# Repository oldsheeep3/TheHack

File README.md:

# HybridSwitcher — ハイブリッドIP映像スイッチャー

既存機材（ATEM Mini）と自作ハードウェア（自作スイッチングモジュール群 + Pico 2W）、
ネットワーク技術（SRT / NDI / WebAPI）を融合した、次世代のハイブリッドIP映像スイッチャーシステム。

PC上に常駐する制御アプリを「脳」とし、複数プロトコル（UVC / NDI / SRT）の映像入力・PiP合成・
仮想カメラ出力・タリー送出・外部機材（ATEM）の遠隔制御を一元化する。DIYでありながらプロ用
スイッチャーに匹敵する多人数オペレーション（メイン/サブ分業）と拡張性を目指す。

> 全体仕様は [`docs/specs/00-system-overview.md`](docs/specs/00-system-overview.md)（親仕様書）を参照。

## システム構成

```text
[ サブ ATEM Mini ] ──(SRT/HDMI/NDI)──→ [ メインPC (常駐App) ] ──(仮想WebCam/HDMI)──→ [ 配信/録画/OBS等 ]
        ▲                                    ▲        │
        │ (ATEM遠隔制御: UDP 9910)            │        │ (UDPタリー: 9999 ブロードキャスト)
        └────────────────────────────────────┘        ▼
                                             ▲   [ ワイヤレスタリー子機(ESP32) ]  [ 赤/緑 LED ]
                                             │ (WebSocket / WebAPI: 8080)
                                    (USB/HID/Serial)
[ 自作コントローラー: Pico 2W ] ──┬── (USB直結) ──→ メインPC
        │                         └── (USB-OTG) ──→ [ スマホ (Web App) ] ──(Wi-Fi/WebSocket)──→ メインPC
        │
        ├─(内部制御: 後日詳細化)──→ [ 各スイッチングモジュール内マイコン ]
        └─(HDMI DDC/I2Cスニッフィング)──→ [ 物理タリー抽出 ]
```

## コンポーネント

| コンポーネント | 場所 | 技術 | 責務 | 個別README / 仕様書 |
| --- | --- | --- | --- | --- |
| PC常駐アプリ | `src/` | C# / .NET 9 + **libobs**(P/Invoke) | 映像入力デコード・PiP合成・仮想カメラ/HDMI出力・WebAPI/WebSocket・UDPタリー送出・ATEM制御 | [App](src/Switcher.App/README.md) / [仕様](docs/specs/pc-switcher-app.md) / [移行](docs/specs/libobs-engine-migration.md) |
| ネイティブ映像エンジン | `native/switcher-engine/` | C/C++ + libobs (GPLv2) | libobs を駆動する `IVideoEngine` の実体（デュアルM/E=obs_view×2・ソース共有・出力・マルチビュー） | [switcher-engine](native/switcher-engine/README.md) |
| Pico 2W コントローラー | `firmware/pico2w-controller/` | Pico SDK (C/C++) | 物理ボタン入力→PC/スマホ送信・モジュール統括・HDMI DDCタリー抽出 | [Firmware](firmware/pico2w-controller/README.md) / [仕様](docs/specs/pico2w-controller-firmware.md) |
| スマホWebブリッジ | `apps/phone-bridge/` | React / TypeScript | Web Serial/WebUSBでPico 2Wを中継・ブラウザ設定UI | [phone-bridge](apps/phone-bridge/README.md) / [仕様](docs/specs/phone-web-bridge.md) |
| ワイヤレスタリー子機 | (未着手) | ESP32 (Arduino/ESP-IDF) | UDPブロードキャスト受信→赤/緑LED点灯 | [仕様](docs/specs/wireless-tally.md) |

### PC常駐アプリの .NET プロジェクト構成（`src/`）

| プロジェクト | 役割 |
| --- | --- |
| `Switcher.Contracts` | 共通インターフェース・DTO（`IVideoEngine` 抽象を含む契約層） |
| `Switcher.Engine` | `IVideoEngine` の実体。ネイティブ `switcher-engine`(libobs) への P/Invoke ＋ テスト用 `FakeVideoEngine` |
| `Switcher.Atem` | ATEM遠隔制御クライアント（UDP 9910） |
| `Switcher.Web` | WebAPI/WebSocketサーバ・UDPタリーブロードキャスト |
| `Switcher.App` | WPFホスト。上記を1つの常駐プロセスに結線するDI合成ルート |

> **libobs 移行**: 旧 `Switcher.Media`(GStreamer/DirectX 合成) / `Switcher.VirtualCam`(自作仮想カメラ) は廃止し、映像パスは libobs に一本化した（[`docs/specs/libobs-engine-migration.md`](docs/specs/libobs-engine-migration.md)）。ネイティブ `switcher-engine.dll` は Windows + OBS でのみビルド/実行し、`.sln` には含まない（テストは `FakeVideoEngine` 注入でヘッドレス実行）。

## リポジトリ構成

```text
.
├── src/                       # PC常駐アプリ (.NET 9) — HybridSwitcher.sln
├── native/switcher-engine/    # ネイティブ映像エンジン (C/C++ + libobs, CMake, .sln外)
├── tests/                     # 上記各プロジェクトのユニットテスト
├── apps/phone-bridge/         # スマホWebブリッジ & 設定UI (React/TS)
├── firmware/pico2w-controller/# Pico 2W コントローラー / タリー抽出ファーム
├── docs/
│   ├── specs/                 # 仕様書（親仕様書 + コンポーネント別）
│   └── tasks/                 # マルチエージェント実装計画・タスク指示書
├── softswitcher*/             # 既存KiCadハードウェア設計（参考資産）
└── HybridSwitcher.sln         # .NET ソリューション
```

## セットアップ（clone 直後に一度）

```sh
./setup.sh          # 共通（.NET / phone-bridge / firmware）
```

```powershell
.\setup.ps1         # Windows で映像エンジンまで動かす場合（追加で実行）
```

clone しただけの状態では、次の理由で初回ビルドが必ず落ちる。`setup.sh` がこれを一括で潰す。

| 落ちる理由 | `setup.sh` の対応 |
| --- | --- |
| `dotnet` / `node` が `~/.bashrc` 経由でしか PATH に乗らない（非ログインシェル・CI では不在） | `DOTNET_ROOT` と nvm を解決して検証。`--install-missing` で .NET SDK を `~/.dotnet` に導入 |
| `firmware/switcher-module/ch32v003fun` サブモジュールが未初期化 | `git submodule update --init --recursive` |
| `scripts` → `.claude/scripts` のリンク切れ（`.claude` は gitignore） | `.claude` を取得してリンクを復旧（失敗しても警告のみ。ビルドには不要） |
| NuGet / npm の依存が未取得 | `dotnet restore` と `npm ci`（CI と同じ lock 厳守） |

主なオプション（何度実行しても同じ結果になる）:

| オプション | 用途 |
| --- | --- |
| `--check` | 検証のみ。取得も生成もせず状態を報告する |
| `--ci` | 対話なし。`.env` を作らず、サブモジュールと `.claude` を触らない |
| `--install-missing` | .NET SDK が無ければ `dotnet-install.sh` で導入する |
| `--skip-submodules` / `--skip-restore` / `--skip-npm` / `--skip-agent-scripts` | 個別スキップ |

未解決の問題が残ると終了コード 1 で終わるので、CI からそのまま呼べる（`./setup.sh --ci`）。

### Windows でネイティブ映像エンジンまで用意する（`setup.ps1`）

Visual Studio で F5 したときの `DllNotFoundException` / `0x8007007E` は、ネイティブの `switcher-engine.dll` が未ビルドなことが原因。この DLL は `.sln` 外の CMake ビルドで、さらにその手前に libobs の import lib **`obs.lib`** が要る。`obs.lib` は **OBS のインストーラには含まれず**、OBS 本体をソースからビルドしないと手に入らない。

`setup.ps1` はその依存の連鎖を通しで面倒を見る。

```text
インストール済み OBS を検出 → 同じ版の obs-studio を clone
  → libobs だけビルド → obs.lib
    → .env に LIBOBS_* を記録
      → build.bat → switcher-engine.dll
        → Switcher.App.csproj が App 出力へ自動コピー（既存の仕組み）
```

| オプション | 用途 |
| --- | --- |
| `-Check` | 検証のみ。clone もビルドも `.env` の書き換えもしない |
| `-ObsVersion <version>` | 使う OBS の版を明示する |
| `-Force` | `obs-studio\` を作り直す（版を切り替えるとき） |
| `-Bundle` | `tools/bundle-obs-runtime.ps1` を呼び、App 出力に `obs-runtime\` を同梱する |
| `-SkipLibobs` / `-SkipEngine` | 個別スキップ |

> **初回は数十分かかる**（obs-studio の clone が数 GB、libobs のビルドがその後）。2 回目以降は済んだ工程を飛ばす。

**バージョンは固定していない。** マネージド側（`ObsRuntime.cs`）は libobs **30.0〜32.99** を受け入れ、範囲外でも警告を出すだけで拒否しない。`setup.ps1` もそれに合わせ、**インストール済み OBS の版を検出してその版のソースをビルドする**。OBS が入っていない場合だけ既定の **32.0.4**（実機検証済み）を使う。

> ⚠️ `obs.lib`（ビルド時）と `obs.dll`（実行時）の版が食い違うと起動失敗・クラッシュする。バージョンを検出に任せるのはこの事故を避けるため。手動で `-ObsVersion` を指定してインストール済みの版と食い違う場合は警告が出る。

**エンドユーザーは OBS のインストールが不要。** `ObsRuntime.Locate()` は実行ファイルの隣の `obs-runtime\` を最優先で見る（`ObsRuntime.cs:83-90`）ので、`-Bundle` で同梱した配布物は自己完結する。OBS インストールが要るのは**ビルドする側**だけ。

> **GPL**: `obs-runtime\` を同梱した配布物は GPL-2.0 になる。[`LICENSE`](LICENSE) / [`THIRD-PARTY-NOTICES.md`](THIRD-PARTY-NOTICES.md) 参照。

### 環境変数（`.env`）

ツールチェーン関連の変数は [`.env.example`](.env.example) をひな形に `.env` へ書く（`setup.sh` が無ければ自動生成する）。`.env` は gitignore 済み。既に export 済みの環境変数が `.env` より優先されるので、CI の `env:` / secrets が上書きされることはない。

> ⚠️ `.env` に書けるのは**ビルド/ツールチェーンの変数だけ**。アプリの動作設定（`AtemIp` / `WebPort` / `ProjectorDisplayIndex` 等）は `src/Switcher.App/appsettings.json` を `System.Text.Json` が直接読む実装で、環境変数は見ない（`Configuration/AppConfigLoader.cs`）。

## ビルド & テスト

### PC常駐アプリ（.NET 9）

> `./setup.sh` 済みでも、`dotnet` が PATH に乗るのは setup.sh の中だけ。呼び出し元のシェルには以下を前置きする。

```sh
export DOTNET_ROOT=$HOME/.dotnet PATH=$HOME/.dotnet:$PATH

dotnet build HybridSwitcher.sln     # 全プロジェクトのビルド
dotnet test  HybridSwitcher.sln     # 全ユニットテスト
```

`Switcher.App` は WPF (`net9.0-windows`) だが `EnableWindowsTargeting` によりLinuxでもCIでも
**コンパイルは可能**。ただしネイティブ `switcher-engine`(libobs) ランタイムは Windows 限定で、
**実行**には Windows 10/11 と下記の起動順が必要。

### ネイティブ映像エンジン（libobs）のビルド & Windows 実起動 — 起動順

`switcher-engine.dll`（`native/switcher-engine/`）は **Windows + OBS 専用**で `.sln` 外。以下が検証済みの順序
（詳細は [switcher-engine README](native/switcher-engine/README.md) / [L-002 タスク](docs/tasks/agent-L-002-native-libobs-engine.md)）。

> 以下は手順の内訳。**通常は [`setup.ps1`](#windows-でネイティブ映像エンジンまで用意するsetupps1) が 1〜2 を自動でやる**ので、手で追う必要があるのは仕組みを確認したいときだけ。

**前提**: Windows / Visual Studio 2022（「C++によるデスクトップ開発」）/ CMake ≥ 3.24 / インストール済み OBS（版は問わない。libobs 30.0〜32.99 が対象）。
以下はすべて **「x64 Native Tools Command Prompt for VS 2022」** から実行する（`cmake`/`cl` に PATH が通る。通常の cmd/PowerShell 不可）。

1. **libobs dev files を用意**（採用 OBS と**同一版**のソースをビルド。インストール済み OBS アプリだけではヘッダ/`obs.lib` が無い）
   ```bat
   git clone --recursive https://github.com/obsproject/obs-studio.git
   rem <version> はインストール済み OBS に合わせる（obs.dll のファイルバージョン）。
   cd obs-studio && git checkout <version> && git submodule update --init --recursive
   cmake --preset windows-x64
   cmake --build build_x64 --config Release --target libobs
   ```
   → `build_x64\libobs\Release\{obs.lib,obs.dll}`、生成ヘッダ `build_x64\config\obsconfig.h`、公開ヘッダ `libobs\`。

2. **`switcher-engine.dll` をビルド**（リポジトリルートで。ヘッダは公開＋生成の2フォルダを `;` 区切りで渡す）
   ```bat
   set OBS=<obs-studio のパス>
   set LIBOBS_INCLUDE_DIR=%OBS%\libobs;%OBS%\build_x64\config
   set LIBOBS_LIB=%OBS%\build_x64\libobs\Release\obs.lib
   native\switcher-engine\build.bat
   ```
   `Switcher.App.csproj` がビルド時に `switcher-engine.dll` を App 出力へ自動コピーする（VS F5/Rebuild でも維持）。

3. **App を起動**（`obs.dll` 等を PATH に通してから）
   - **Visual Studio**: 構成 `Debug`/**`x64`** → `Switcher.App` をスタートアップに → プロパティ「デバッグ」→ デバッグ起動プロファイルUIで環境変数
     `PATH = C:\Program Files\obs-studio\bin\64bit;%PATH%`（版一致のインストール済み OBS）→ **F5**。
   - **コマンドライン**:
     ```bat
     dotnet build src\Switcher.App\Switcher.App.csproj -c Release
     set PATH=%OBS%\build_x64\rundir\Release\bin\64bit;%PATH%
     src\Switcher.App\bin\x64\Release\net9.0-windows\Switcher.App.exe
     ```

> **前提/注意**
> - `obs.dll` + `data\` + プラグイン + `libobs-d3d11.dll` が PATH 上で到達可能、かつ import lib(`obs.lib`) と**同一版**であること（不一致は起動失敗/クラッシュ）。
> - **L-002 未完のうちは `engine_startup` が `obs_reset_video` で失敗**する（libobs データパス未配線。[L-002 タスク](docs/tasks/agent-L-002-native-libobs-engine.md)の「実機検証で判明した実装ポイント」参照）。
> - ネイティブ抜きで App を動かすなら DI（`src/Switcher.App/Composition/ServiceCollectionExtensions.cs`）を `FakeVideoEngine` に差し替える。

### スマホWebブリッジ（React/TS）

```sh
cd apps/phone-bridge
npm install
npm run dev      # 開発サーバ
npm run build    # プロダクションビルド
npm test         # vitest
```

### Pico 2W ファームウェア

I/Oに依存しないロジックはホストの `gcc` でユニットテスト可能（Pico SDK不要）。

```sh
cd firmware/pico2w-controller/test
make             # ビルド + 実行（全テスト green で終了コード0）
```

実機向けクロスビルド（Pico SDK / `arm-none-eabi` ツールチェーン必要）は
[`firmware/pico2w-controller/README.md`](firmware/pico2w-controller/README.md) を参照。

### CI（GitHub Actions）

[`.github/workflows/ci.yml`](.github/workflows/ci.yml) が **全 PR**（タスク → 親Epic の PR も含む）と
`main` / `develop` への push で走る。すべて `ubuntu-latest`。

| ジョブ | 内容 |
| --- | --- |
| `.NET` | `dotnet build -c Release -warnaserror` → `dotnet format --verify-no-changes` → `dotnet test`（結果 `.trx` をアーティファクト化） |
| `phone-bridge` | `npm ci` → `npm run lint`(eslint) → `npm run build`(`tsc -b` 型チェック + vite) → `npm test`(vitest)、`dist/` をアーティファクト化 |
| `firmware` | `firmware/pico2w-controller/test` と `firmware/switcher-module/test` のホストテスト（gcc、`-Werror`） |

ブランチ保護の必須チェックには集約ジョブ **`All checks`** 1つを指定すればよい。

**CI が走るのは個人リポジトリ（public）だけ。** ミラー先の `NxTEND-THE-HACK/2026-Team-38` は
Free org の private リポジトリで Actions のランナーが割り当てられず、どのジョブも 0 ステップの
まま即座に失敗する（ワークフロー側の問題ではなく org の Actions 枠の問題で、修正には org 管理者
による支払い設定・repo の public 化・セルフホストランナー登録のいずれかが要る）。そのため全ジョブに
`if: github.repository_owner != 'NxTEND-THE-HACK'` を付けて向こうでは skip させている。ジョブレベルの
`if` はランナー要求より前に評価されるので、skip されたジョブは失敗扱いにならない。

CI 対象外（ローカル/Windows でのみ検証可能）:

- `native/switcher-engine`（libobs 依存・Windows + OBS 専用・`.sln` 外）と、それを要する App の実起動
- `web/build-preview.ps1`（Windows PowerShell 前提のパス処理）
- `apps/phone-bridge` の Prettier 整形チェック（既存ファイルが未整形のため未導入。`npm run format` で一括整形後に追加可能）

### ミラー（個人リポジトリ → ハッカソン用リポジトリ）

開発を個人アカウントの public リポジトリ（`oldsheeep3/TheHack`）で行い、ハッカソン用 private
リポジトリ（`NxTEND-THE-HACK/2026-Team-38`）へ push のたびに反映する。**片方向**（個人 → ハッカソン用）。

**ミラー先へ書けるトークンは GitHub に預けない。** 実際に push するのは tailnet 上の VPS（`gh`
ログイン済み）で、自分の資格情報を使う。GitHub Actions はその VPS に SSH して起動をかけるだけ
なので、この public リポジトリに置く secret は tailnet への参加情報と SSH 鍵だけで済む。

`.github/` を含め、履歴をそのまま送る（コミット SHA も個人リポジトリ側と一致する）。ミラー先では
CI を走らせないよう、[`ci.yml`](.github/workflows/ci.yml) と [`mirror.yml`](.github/workflows/mirror.yml)
の両方がリポジトリのオーナーを見てジョブを skip する。

```text
手元 ── git push origin ──→ oldsheeep3/TheHack (public)
                              ├ Actions: ci.yml（green になったら↓を起動）
                              └ Actions: mirror.yml
                                  ├ tailscale/github-action で tailnet に参加
                                  └ ssh ──→ VPS: mirror-sync <branch>
                                              ├ 個人リポジトリから fetch（~/mirror/TheHack.git）
                                              └ mirror.sh  … mirror/X を push + PR 作成 + マージ
                                                              ↓
                                              NxTEND-THE-HACK/2026-Team-38 (private)
```

ブランチ `X` を push すると:

0. まず CI が走り、**green で終わったときだけ**ミラーが起動する（`workflow_run` トリガー）。
   赤い場合・CI が走らないブランチは、直さない限りミラーされない
1. [`.github/workflows/mirror.yml`](.github/workflows/mirror.yml) が tailnet に ephemeral ノードとして参加し、
   VPS へ SSH して [`mirror-sync X`](tools/mirror/mirror-sync) を実行する（CI が通った `X` だけが対象）
2. VPS が個人リポジトリから `X` を fetch し、[`tools/mirror/mirror.sh`](tools/mirror/mirror.sh) を呼ぶ
3. ミラー先の **`mirror/X`**（ミラー専用ブランチ）へ push
4. `mirror/X` → `X` の PR を作成（既にオープンならそれを使う）し、**マージコミットでマージする**

起点が GitHub 側にあるので、どのマシンから push しても（GitHub 上で直接編集しても）ミラーされる。
同期するのは CI が通ったそのブランチだけ。全ブランチ + 全タグをまとめて送るのは手動実行のとき。

ミラー先の `main` / `develop` へ直接 push も force push もしない。force は「手元で rebase / amend して
`mirror/X` が fast-forward できなくなった」場合のフォールバックとして `mirror/*` に対してのみ使う。
ミラー先の ref を削除することはないので、ブランチ削除は同期されない。

Actions が使えないとき（ワークフローの失敗、tailnet の不調、初回の一括コピー）は VPS 側で
`mirror-sync` を直接実行すれば追いつく。

| 場所 | もの | 役割 |
| --- | --- | --- |
| GitHub | `.github/workflows/mirror.yml` | tailnet に参加して VPS へ SSH し `mirror-sync` を起動 |
| VPS | `~/mirror/TheHack.git` | 中継用の bare リポジトリ（remote: `personal` / `hackathon`） |
| VPS | `~/mirror/mirror.sh` | `mirror/X` の push・PR 作成・マージ（[`tools/mirror/mirror.sh`](tools/mirror/mirror.sh)） |
| VPS | `~/.local/bin/mirror-sync` | 個人リポジトリから取り込んで同期（[`tools/mirror/mirror-sync`](tools/mirror/mirror-sync)） |

セットアップ:

```sh
# VPS 側（gh でログイン済み・gh auth setup-git 済みであること）
scp -r tools/mirror <vps>:~/mirror-install
ssh <vps> 'bash ~/mirror-install/install-vps.sh'

# CI 用の SSH 鍵を作って公開鍵を VPS に置く
ssh-keygen -t ed25519 -N '' -f mirror_ci
ssh-copy-id -i mirror_ci.pub <vps>

# 手動同期（全ブランチ + 全タグ / ブランチ指定）
ssh sheep 'bash -lc mirror-sync'
ssh sheep 'bash -lc "mirror-sync develop"'
```

個人リポジトリの Settings → Secrets and variables → Actions に登録する secret:

| secret | 中身 |
| --- | --- |
| `TS_CLIENT` / `TS_SECRET` | Tailscale の OAuth クライアント ID / シークレット（scope `auth_keys` write / tag `tag:ci`） |
| `SSH_HOST` / `SSH_USER` | VPS の tailnet アドレス（100.x or MagicDNS 名）とログインユーザー名 |
| `SSH_KEY` | ログインに使う**秘密鍵**（`mirror_ci` の中身。公開鍵は VPS の `authorized_keys` へ） |
| `SSH_KNOWN_HOSTS` | VPS のホスト鍵（`ssh-keyscan <host>` の出力）。任意だが推奨 |

tailnet の ACL で `tag:ci` から VPS の 22/tcp を許可しておくこと。

> - マージは **マージコミット**で行う（squash / rebase merge だと merge-base が進まず、次回の
>   PR に同じコミットが再び載る）。ブランチ保護で弾かれた場合は `gh pr merge --admin` で通す。
> - ミラー先に同名ブランチが無いと PR は作れない（`mirror/X` の push だけ行い notice を出す）。
>   その場合はミラー先で `mirror/X` からブランチを作る。
> - 手動で `mirror-sync` を叩くときは Actions の実行と重ならないようにする（作業リポジトリを共有
>   していて、排他はしていない）。
> - `workflow_run` は**デフォルトブランチにあるワークフローファイル**しか起動しない。`mirror.yml`
>   は `main` にも入っている必要がある（`develop` だけに置いても発火しない）。
> - CI の push トリガーは `main` / `develop` だけなので、作業ブランチを直接 push してもミラーは
>   起動しない（PR を出せば CI は走るが、`pull_request` 由来の実行はミラーの対象外）。作業ブランチを
>   今すぐミラーしたいときは VPS で `mirror-sync <branch>` を叩くか、Actions から手動実行する。
> - ミラーの実行は `concurrency` で 1 本に絞っている。実行中 + 待機中がいる状態でさらに CI が
>   green になると待機中が追い出され、そのブランチは次の CI green まで待つ。
> - `.github/workflows/` も同期するので、VPS の `gh` ログインには **`workflow` スコープ**が要る
>   （`gh auth refresh -h github.com -s workflow`）。無いと push が拒否される。
> - タグは手動同期（引数なしの `mirror-sync`）のときにまとめて送る。ミラー先で既に別のコミットを
>   指しているタグは上書きしない。

## 共通プロトコル / ポート

各コンポーネントは親仕様書 §4 の共通定義に準拠する。

| ポート | プロトコル | 用途 |
| --- | --- | --- |
| 8080 | HTTP/WebSocket | 設定WebAPI・コントローラー入力受信 |
| 9000 | SRT (Listener) | 映像入力（ATEM PGM等） |
| 9999 | UDP broadcast | タリー配信（`255.255.255.255:9999`） |
| 9910 | UDP | ATEM遠隔制御（ATEM純正プロトコル） |

詳細（イベントペイロード・設定変更API・タリーペイロード）は
[`docs/specs/00-system-overview.md`](docs/specs/00-system-overview.md) §4 を参照。

## ドキュメント

- **技術仕様（現行実装）**: [`docs/spec/technical-overview.md`](docs/spec/technical-overview.md)（詳細） /
  [`docs/spec/summary.md`](docs/spec/summary.md)（要約） / [`docs/slides/switcher.md`](docs/slides/switcher.md)（Marp）
- **配布サイト**: [`web/`](web/) — LP + 使い方（`web/build-preview.ps1` で1ファイルのプレビューを生成）
- **ライセンス**: GPL-2.0-or-later（[`LICENSE`](LICENSE) / [`THIRD-PARTY-NOTICES.md`](THIRD-PARTY-NOTICES.md)）
- **仕様書**: [`docs/specs/`](docs/specs/) — 親仕様書 + コンポーネント別詳細仕様
- **実装計画 / タスク**: [`docs/tasks/`](docs/tasks/) — マルチエージェント実装のオーケストレーション計画とタスク指示書

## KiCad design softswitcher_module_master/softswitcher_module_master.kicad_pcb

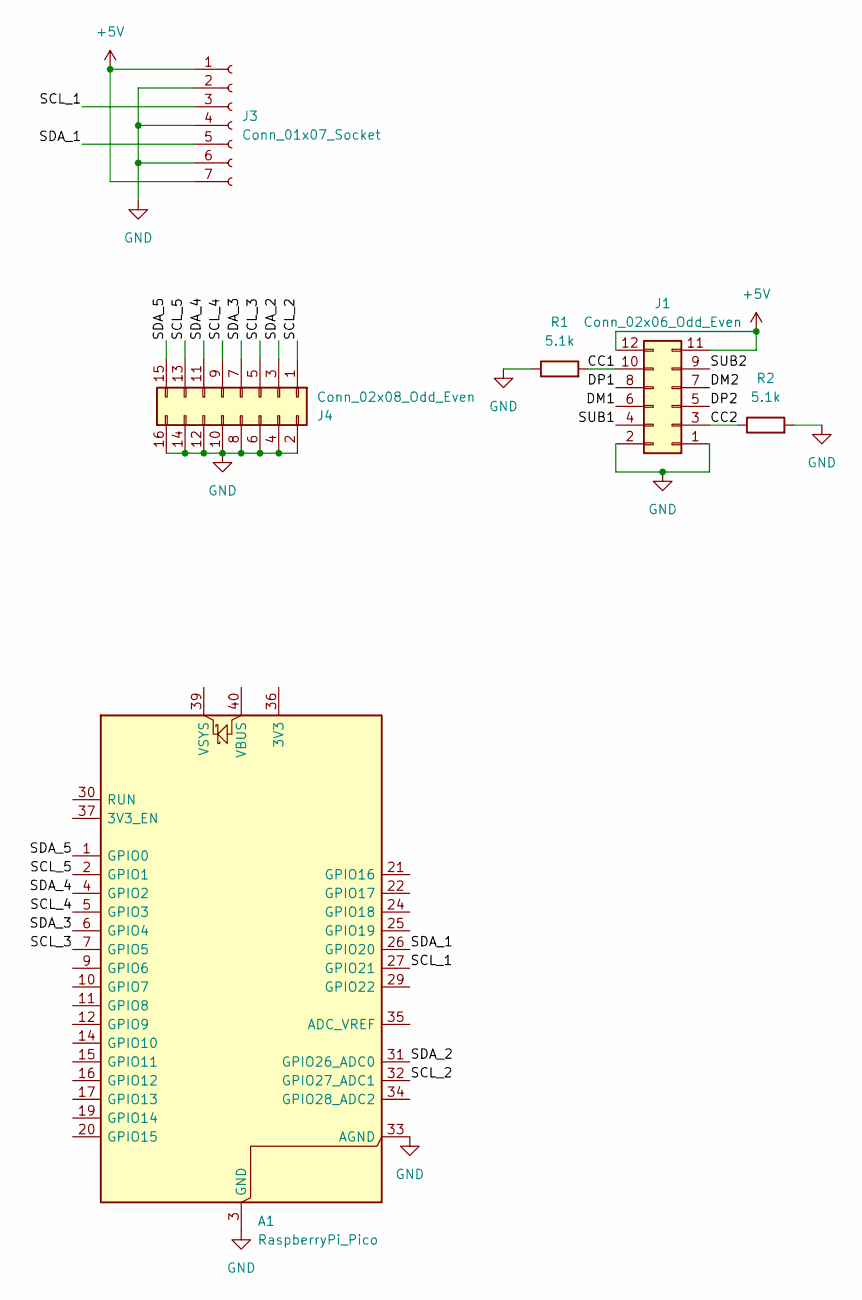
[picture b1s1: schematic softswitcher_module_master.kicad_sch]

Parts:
A1: RaspberryPi_Pico; RaspberryPi_Pico_Common_THT
J1: Conn_02x06_Odd_Even; PinHeader_2x06_P2.54mm_Vertical
J3: Conn_01x07_Socket; PinSocket_1x07_P2.54mm_Horizontal
J4: Conn_02x08_Odd_Even; PinSocket_2x08_P2.54mm_Horizontal
R1, R2: 5.1k; R_Axial_DIN0309_L9.0mm_D3.2mm_P12.70mm_Horizontal

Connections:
+5V: J1.11, J1.12, J3.1, J3.7
/CC1: J1.10, R1.2
/CC2: J1.3, R2.1
/DM1: J1.6
/DM2: J1.7
/DP1: J1.8
/DP2: J1.5
/SCL_1: A1.27 (GPIO21), J3.3
/SCL_2: A1.32 (GPIO27_ADC1), J4.1
/SCL_3: A1.7 (GPIO5), J4.5
/SCL_4: A1.5 (GPIO3), J4.9
/SCL_5: A1.2 (GPIO1), J4.13
/SDA_1: A1.26 (GPIO20), J3.5
/SDA_2: A1.31 (GPIO26_ADC0), J4.3
/SDA_3: A1.6 (GPIO4), J4.7
/SDA_4: A1.4 (GPIO2), J4.11
/SDA_5: A1.1 (GPIO0), J4.15
/SUB1: J1.4
/SUB2: J1.9
GND: A1.3 (GND), A1.8 (GND), A1.13 (GND), A1.18 (GND), A1.23 (GND), A1.28 (GND), A1.33 (AGND), A1.38 (GND), J1.1, J1.2, J3.2, J3.4, J3.6, J4.2, J4.4, J4.6, J4.8, J4.10, J4.12, J4.14, J4.16, R1.1, R2.2

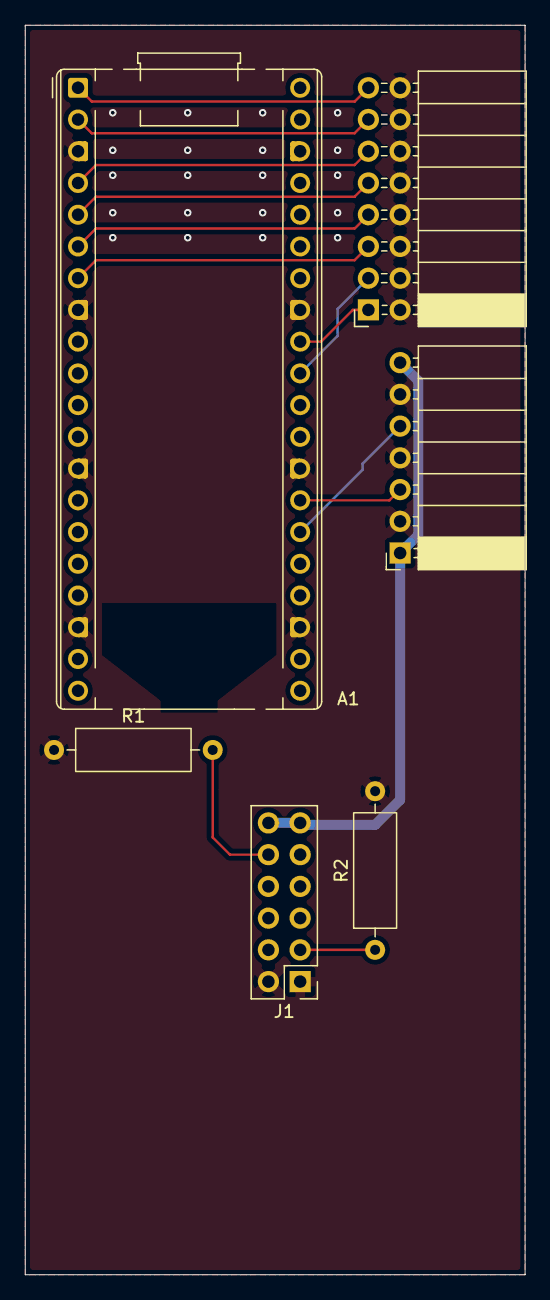
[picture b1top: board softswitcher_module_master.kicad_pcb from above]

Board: 2 copper layers, 40.0 x 100.0 mm, 6 parts (0 on the bottom side), 14 nets.

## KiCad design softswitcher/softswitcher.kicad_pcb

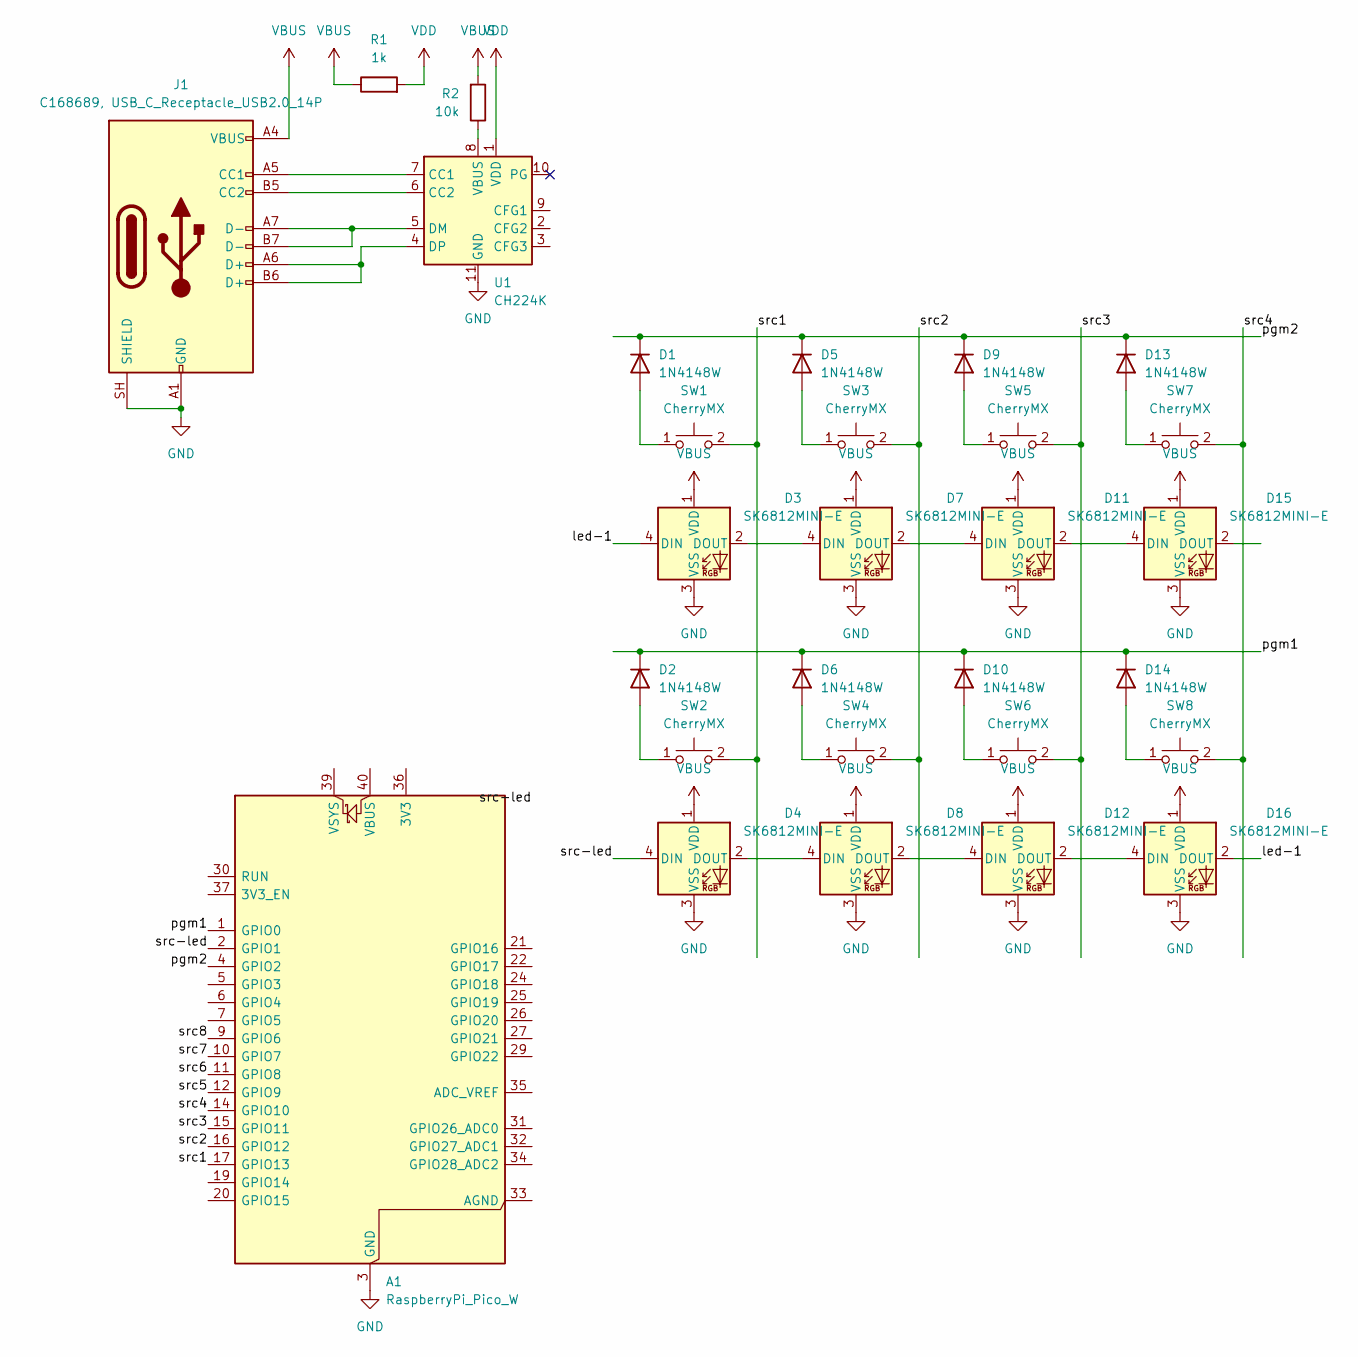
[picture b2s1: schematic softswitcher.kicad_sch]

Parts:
A1: RaspberryPi_Pico_W; RaspberryPi_Pico_Common_THT
D1, D2, D5, D6, D9, D10, D13, D14: 1N4148W; D_SOD-123
D3, D4, D7, D8, D11, D12, D15, D16: SK6812MINI-E; MX_SK6812MINI-E
J1: C168689, USB_C_Receptacle_USB2.0_14P; USB_C_Receptacle_GCT_USB4105-xx-A_16P_TopMnt_Horizontal
R1: 1k; R_1206_3216Metric
R2: 10k; R_1206_3216Metric
SW1, SW2, SW3, SW4, SW5, SW6, SW7, SW8: CherryMX; CherryMX_1.00u
U1: CH224K; SSOP-10-1EP_3.9x4.9mm_P1mm_EP2.1x3.3mm

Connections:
/led-1: D3.4 (DIN), D16.2 (DOUT)
/pgm1: A1.1 (GPIO0), D2.1 (K), D6.1 (K), D10.1 (K), D14.1 (K)
/pgm2: A1.4 (GPIO2), D1.1 (K), D5.1 (K), D9.1 (K), D13.1 (K)
/src1: A1.17 (GPIO13), SW1.2, SW2.2
/src2: A1.16 (GPIO12), SW3.2, SW4.2
/src3: A1.15 (GPIO11), SW5.2, SW6.2
/src4: A1.14 (GPIO10), SW7.2, SW8.2
/src5: A1.12 (GPIO9)
/src6: A1.11 (GPIO8)
/src7: A1.10 (GPIO7)
/src8: A1.9 (GPIO6)
/src-led: A1.2 (GPIO1), D4.4 (DIN)
GND: A1.3 (GND), A1.8 (GND), A1.13 (GND), A1.18 (GND), A1.23 (GND), A1.28 (GND), A1.38 (GND), D3.3 (VSS), D4.3 (VSS), D7.3 (VSS), D8.3 (VSS), D11.3 (VSS), D12.3 (VSS), D15.3 (VSS), D16.3 (VSS), J1.A1 (GND), J1.A12 (GND), J1.B1 (GND), J1.B12 (GND), J1.SH (SHIELD), U1.11 (GND)
unnamed: D1.2 (A), SW1.1
unnamed: D2.2 (A), SW2.1
unnamed: D3.2 (DOUT), D7.4 (DIN)
unnamed: D4.2 (DOUT), D8.4 (DIN)
unnamed: D5.2 (A), SW3.1
unnamed: D6.2 (A), SW4.1
unnamed: D9.2 (A), SW5.1
unnamed: D10.2 (A), SW6.1
unnamed: D7.2 (DOUT), D11.4 (DIN)
unnamed: D11.2 (DOUT), D15.4 (DIN)
unnamed: D8.2 (DOUT), D12.4 (DIN)
unnamed: D12.2 (DOUT), D16.4 (DIN)
unnamed: D13.2 (A), SW7.1
unnamed: D14.2 (A), SW8.1
unnamed: J1.A5 (CC1), U1.7 (CC1)
unnamed: J1.B5 (CC2), U1.6 (CC2)
unnamed: J1.A7 (D-), J1.B7 (D-), U1.5 (DM)
unnamed: J1.A6 (D+), J1.B6 (D+), U1.4 (DP)
unnamed: R2.1, U1.8 (VBUS)
VBUS: D3.1 (VDD), D4.1 (VDD), D7.1 (VDD), D8.1 (VDD), D11.1 (VDD), D12.1 (VDD), D15.1 (VDD), D16.1 (VDD), J1.A4 (VBUS), J1.A9 (VBUS), J1.B4 (VBUS), J1.B9 (VBUS), R1.1, R2.2
VDD: R1.2, U1.1 (VDD)

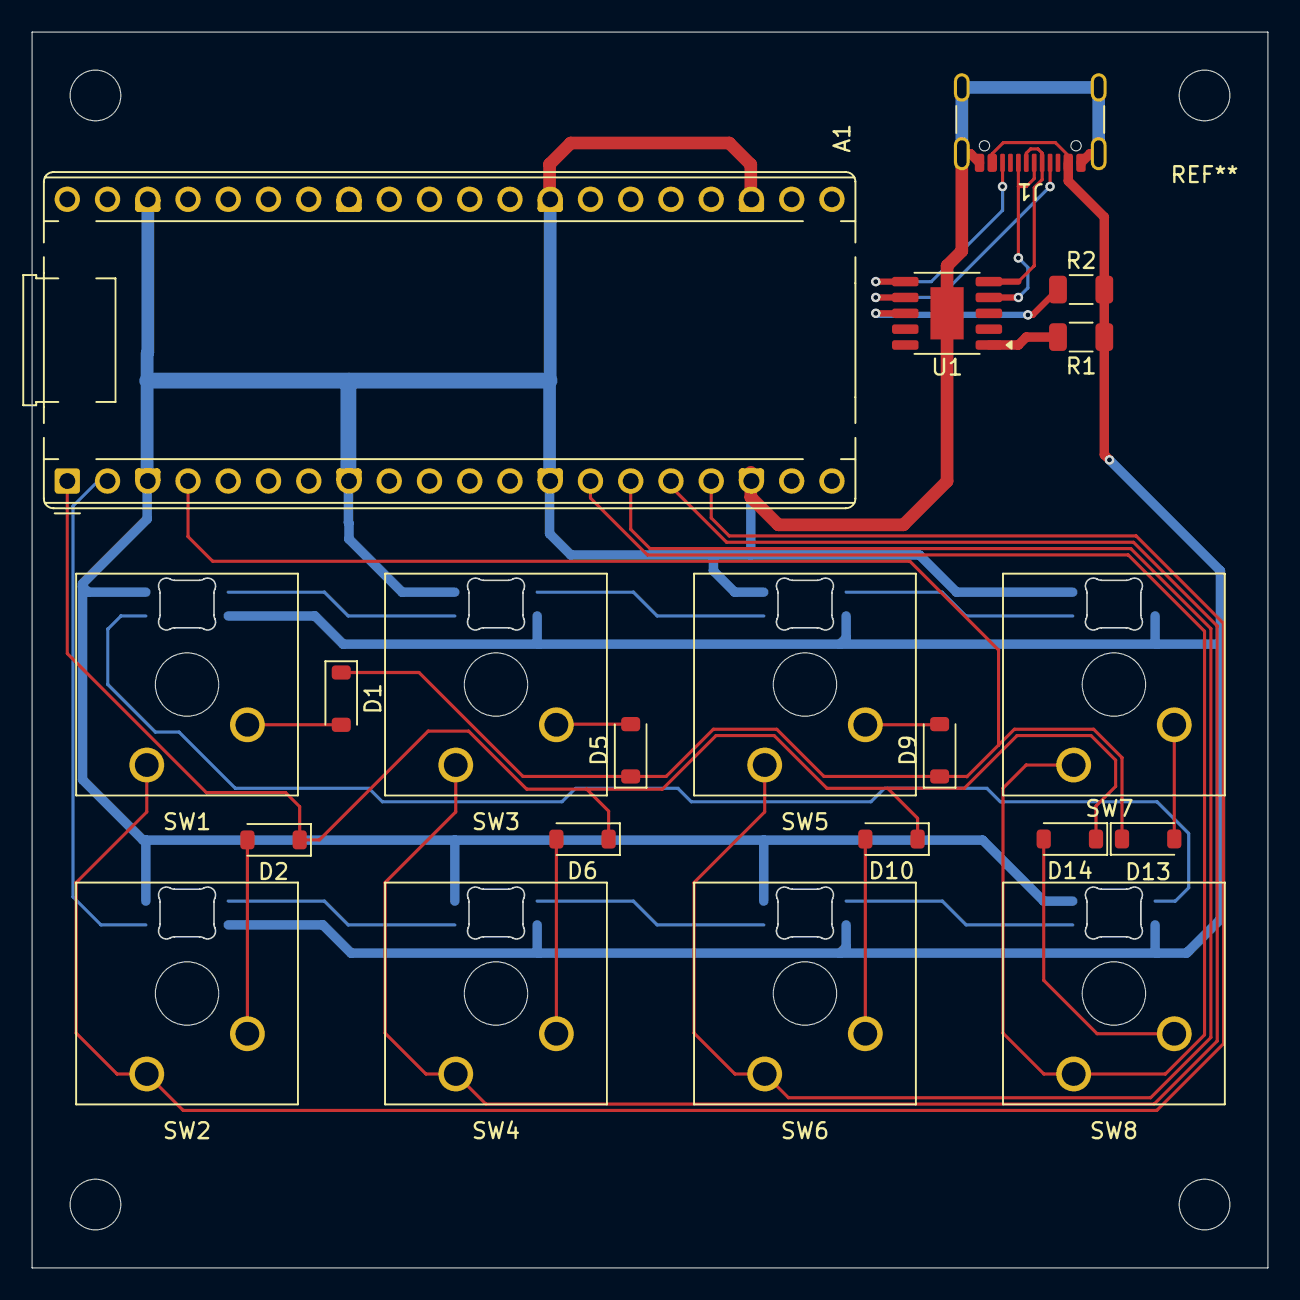
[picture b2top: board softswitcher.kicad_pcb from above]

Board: 2 copper layers, 78.0 x 78.0 mm, 29 parts (0 on the bottom side), 30 nets.

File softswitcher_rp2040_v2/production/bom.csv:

Designator,Footprint,Quantity,Value,LCSC Part #
A1,RaspberryPi_Pico_Common_THT,1,RaspberryPi_Pico_W,
"D1, D10, D13, D14, D2, D5, D6, D9",D_SOD-123,8,1N4148W,
"D11, D12, D15, D16, D3, D4, D7, D8",MX_SK6812MINI-E,8,SK6812MINI-E,
J1,USB_C_Receptacle_GCT_USB4105-xx-A_16P_TopMnt_Horizontal,1,USB_C_Receptacle_USB2.0_14P,
R1,1206,1,1k,
R2,1206,1,10k,
"SW1, SW2, SW3, SW4, SW5, SW6, SW7, SW8",CherryMX_1.00u,8,CherryMX,
U1,SSOP-10-1EP_3.9x4.9mm_P1mm_EP2.1x3.3mm,1,CH224K,

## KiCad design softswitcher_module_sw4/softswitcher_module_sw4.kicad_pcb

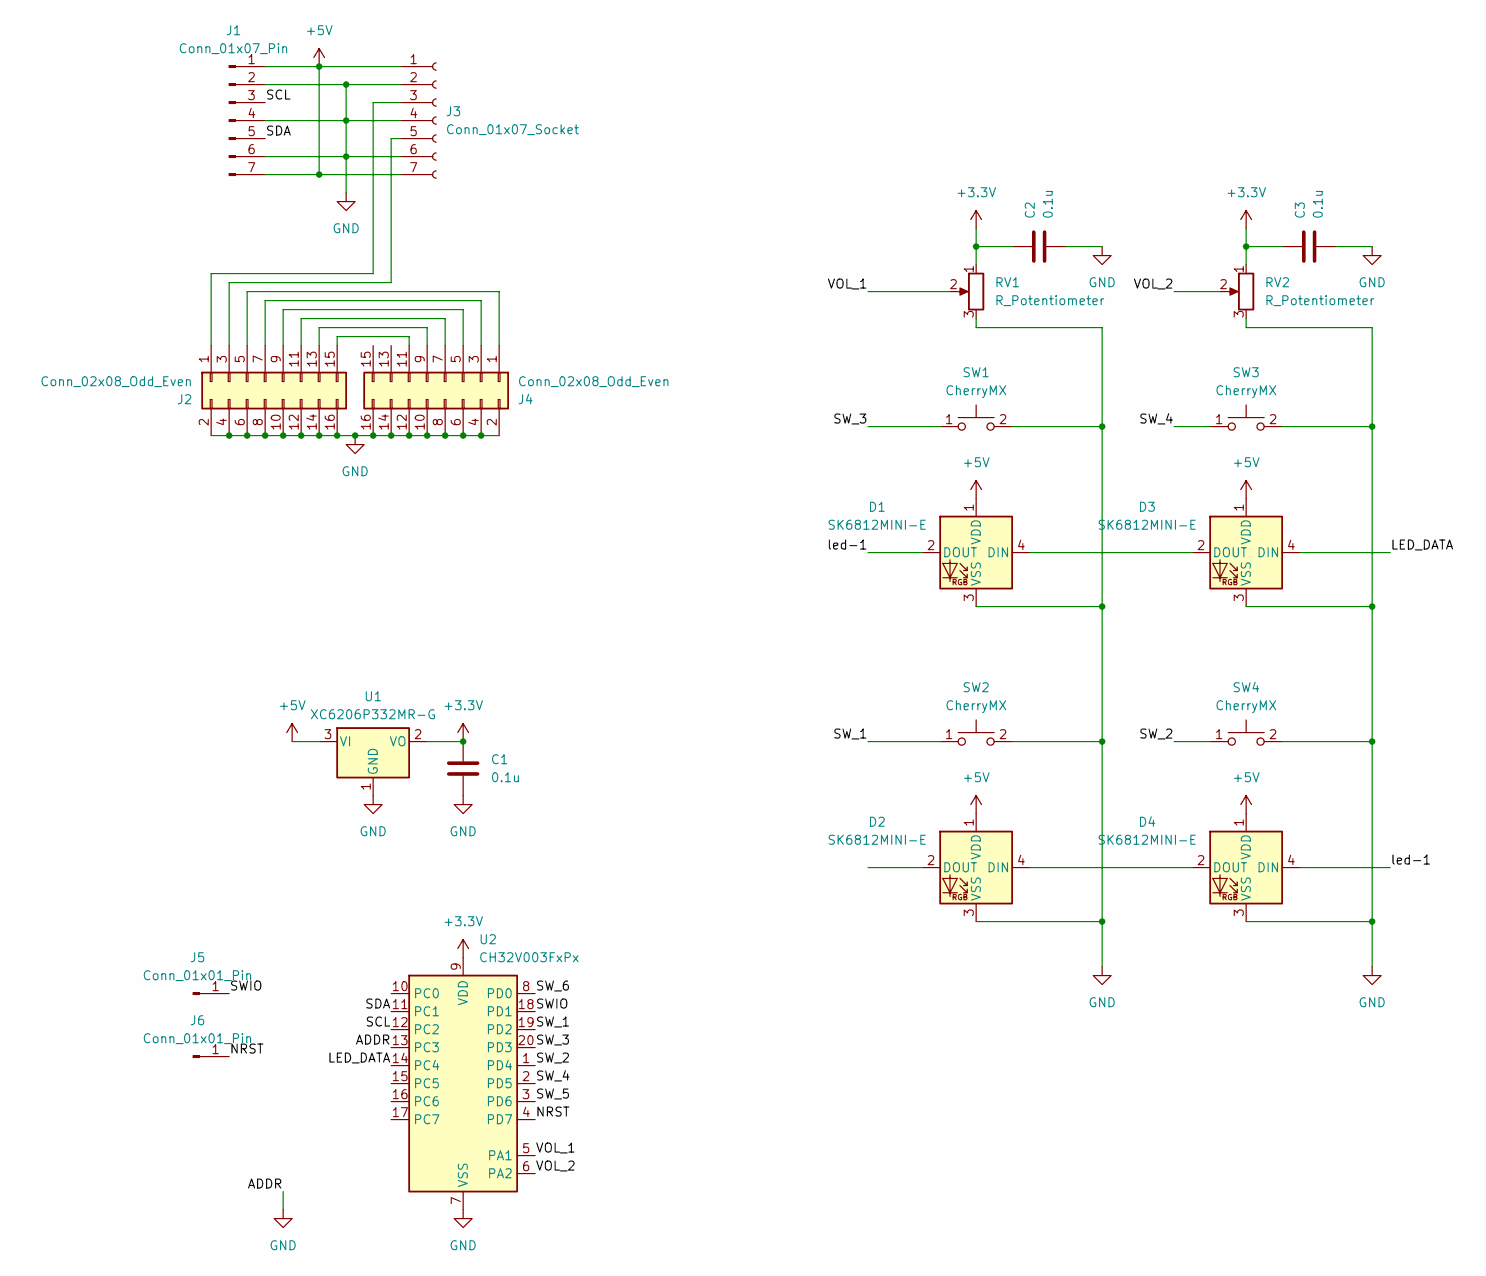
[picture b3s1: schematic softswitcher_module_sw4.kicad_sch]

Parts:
C1, C2, C3: 0.1u; C_0402_1005Metric
D1, D2, D3, D4: SK6812MINI-E; MX_SK6812MINI-E
J1: Conn_01x07_Pin; PinHeader_1x07_P2.54mm_Horizontal
J2: Conn_02x08_Odd_Even; PinHeader_2x08_P2.54mm_Horizontal
J3: Conn_01x07_Socket; PinSocket_1x07_P2.54mm_Horizontal
J4: Conn_02x08_Odd_Even; PinSocket_2x08_P2.54mm_Horizontal
J5, J6: Conn_01x01_Pin; PinHeader_1x01_P2.54mm_Vertical
RV1, RV2: R_Potentiometer; Potentiometer_Alps_RK09K_Single_Vertical
SW1, SW2, SW3, SW4: CherryMX; CherryMX_1.00u
U1: XC6206P332MR-G; SOT-23-3
U2: CH32V003FxPx; TSSOP-20_4.4x6.5mm_P0.65mm

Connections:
+3.3V: C1.1, C2.1, C3.1, RV1.1, RV2.1, U1.2 (VO), U2.9 (VDD)
+5V: D1.1 (VDD), D2.1 (VDD), D3.1 (VDD), D4.1 (VDD), J1.1, J1.7, J3.1, J3.7, U1.3 (VI)
/LED_DATA: D3.4 (DIN), U2.14 (PC4)
/NRST: J6.1 (Pin_1_1), U2.4 (PD7)
/SCL: J1.3, U2.12 (PC2)
/SDA: J1.5, U2.11 (PC1)
/SWIO: J5.1 (Pin_1_1), U2.18 (PD1)
/SW_1: SW2.1, U2.19 (PD2)
/SW_2: SW4.1, U2.1 (PD4)
/SW_3: SW1.1, U2.20 (PD3)
/SW_4: SW3.1, U2.2 (PD5)
/SW_5: U2.3 (PD6)
/SW_6: U2.8 (PD0)
/VOL_1: RV1.2, U2.5 (PA1)
/VOL_2: RV2.2, U2.6 (PA2)
/led-1: D1.2 (DOUT), D4.4 (DIN)
GND: C1.2, C2.2, C3.2, D1.3 (VSS), D2.3 (VSS), D3.3 (VSS), D4.3 (VSS), J1.2, J1.4, J1.6, J2.2, J2.4, J2.6, J2.8, J2.10, J2.12, J2.14, J2.16, J3.2, J3.4, J3.6, J4.2, J4.4, J4.6, J4.8, J4.10, J4.12, J4.14, J4.16, RV1.3, RV2.3, SW1.2, SW2.2, SW3.2, SW4.2, U1.1 (GND), U2.7 (VSS), U2.13 (PC3)
unnamed: D1.4 (DIN), D3.2 (DOUT)
unnamed: D2.4 (DIN), D4.2 (DOUT)
unnamed: J2.1, J3.3
unnamed: J2.3, J3.5
unnamed: J2.5, J4.1
unnamed: J2.7, J4.3
unnamed: J2.9, J4.5
unnamed: J2.11, J4.7
unnamed: J2.13, J4.9
unnamed: J2.15, J4.11

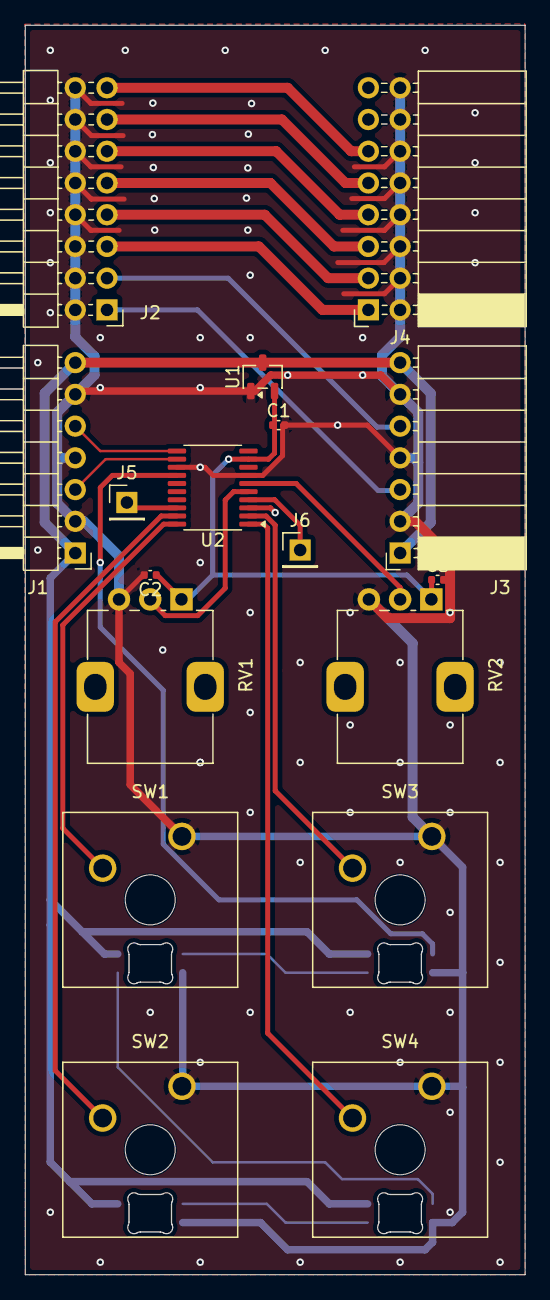
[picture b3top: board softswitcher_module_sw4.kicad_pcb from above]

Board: 2 copper layers, 40.0 x 100.0 mm, 21 parts (0 on the bottom side), 25 nets.

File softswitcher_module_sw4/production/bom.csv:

Designator,Footprint,Quantity,Value,LCSC Part #
"C1, C2, C3",0402,3,0.1u,
J1,PinHeader_1x07_P2.54mm_Horizontal,1,Conn_01x07_Pin,
J2,PinHeader_2x08_P2.54mm_Horizontal,1,Conn_02x08_Odd_Even,
J3,PinSocket_1x07_P2.54mm_Horizontal,1,Conn_01x07_Socket,
J4,PinSocket_2x08_P2.54mm_Horizontal,1,Conn_02x08_Odd_Even,
"J5, J6",PinHeader_1x01_P2.54mm_Vertical,2,Conn_01x01_Pin,
"SW1, SW2, SW3, SW4",CherryMX_1.00u,4,CherryMX,
U1,SOT-23-3,1,XC6206P332MR-G,
U2,TSSOP-20_4.4x6.5mm_P0.65mm,1,CH32V003FxPx,

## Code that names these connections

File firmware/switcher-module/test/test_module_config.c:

// module_config.h の定数実体 (module_config.c) がSW/VR/バックライト/I2Cベースアドレスの
// 契約どおりに提供されていることを検証する。ピン番号は基板 softswitcher_module_sw4
// (CH32V003F4P6, TSSOP-20) の実配線。

#include <assert.h>
#include <stdio.h>

#include "module_config.h"

// ch32fun のピンエンコード (ポート番号<<4 | ピン番号) の実値。ch32fun.h をincludeせずに
// 検証できるよう期待値をリテラルで置く (ch32fun定数との一致は switches.c /
// backlight.c / i2c_slave.c の _Static_assert がクロスビルド時に保証する)。
#define EXPECT_PA1 0x01
#define EXPECT_PC1 0x21
#define EXPECT_PC2 0x22
#define EXPECT_PC4 0x24
#define EXPECT_PD2 0x32
#define EXPECT_PD3 0x33
#define EXPECT_PD4 0x34
#define EXPECT_PD5 0x35

int main(void) {
    assert(MAX_MODULES == 8);
    assert(I2C_BASE_ADDR == 0x30);

    // ピンエンコードが ch32fun (GpioOf: pin>>4 でポート, pin&0xf でビット) と同形式。
    assert(MODULE_PIN(MODULE_PORT_A, 1) == EXPECT_PA1);
    assert(MODULE_PIN(MODULE_PORT_C, 4) == EXPECT_PC4);
    assert(MODULE_PIN(MODULE_PORT_D, 2) == EXPECT_PD2);

    // I2Cスレーブ: 11pin(PC1)=SDA / 12pin(PC2)=SCL (I2C1のシリコン固定ピン)。
    assert(MODULE_I2C_SDA_PIN == EXPECT_PC1);
    assert(MODULE_I2C_SCL_PIN == EXPECT_PC2);

    // SW: 4個の独立入力。SW_1=19pin(PD2) / SW_2=1pin(PD4) / SW_3=20pin(PD3) / SW_4=2pin(PD5)。
    assert(SW_COUNT == 4);
    assert(SW_BIT_SW1 == 0);
    assert(SW_BIT_SW2 == 1);
    assert(SW_BIT_SW3 == 2);
    assert(SW_BIT_SW4 == 3);
    assert(SW_BIT_PGM1_SRC1 == SW_BIT_SW1);
    assert(SW_BIT_PGM1_SRC2 == SW_BIT_SW2);
    assert(SW_BIT_PGM2_SRC1 == SW_BIT_SW3);
    assert(SW_BIT_PGM2_SRC2 == SW_BIT_SW4);
    assert(sizeof(SW_PINS) / sizeof(SW_PINS[0]) == SW_COUNT);
    assert(SW_PINS[SW_BIT_SW1] == EXPECT_PD2);
    assert(SW_PINS[SW_BIT_SW2] == EXPECT_PD4);
    assert(SW_PINS[SW_BIT_SW3] == EXPECT_PD3);
    assert(SW_PINS[SW_BIT_SW4] == EXPECT_PD5);

    // VR: VOL1=5pin(PA1)=ADCチャネル1 / VOL2=6pin(PA2)=ADCチャネル0。
    assert(VR_COUNT == 2);
    assert(sizeof(VR_ADC_CHANNELS) / sizeof(VR_ADC_CHANNELS[0]) == VR_COUNT);
    assert(VR_ADC_CHANNELS[VR_SRC1_INDEX] == 1);
    assert(VR_ADC_CHANNELS[VR_SRC2_INDEX] == 0);

    // バックライト: LED_DATA=14pin(PC4), SK6812MINI-E ×4。
    assert(BACKLIGHT_LED_COUNT == 4);
    assert(BACKLIGHT_DATA_PIN == EXPECT_PC4);
    assert(MODULE_REG_BACKLIGHT_LEN == BACKLIGHT_LED_COUNT * 3);

    // モジュール番号ストラップは実基板に無く、全モジュールが 0x30 固定で待ち受ける。
    assert(MODULE_INDEX_FIXED == 0);

    // ピンの重複割当が無いこと (SW×4 + LED_DATA + I2C×2)。
    const uint8_t all_pins[] = {
        SW_PINS[0], SW_PINS[1], SW_PINS[2], SW_PINS[3],
        BACKLIGHT_DATA_PIN, MODULE_I2C_SDA_PIN, MODULE_I2C_SCL_PIN,
    };
    const unsigned all_pin_count = sizeof(all_pins) / sizeof(all_pins[0]);
    for (unsigned i = 0; i < all_pin_count; i++) {
        for (unsigned j = i + 1; j < all_pin_count; j++) {
            assert(all_pins[i] != all_pins[j]);
        }
    }
    printf("test_module_config: OK\n");
    return 0;
}

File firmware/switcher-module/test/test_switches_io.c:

// switches.c (GPIO依存のSW直読み) を stub/ch32fun.h 経由でホスト上で検証する。
// 実基板 (softswitcher_module_sw4) の配線 SW_1=19pin(PD2) / SW_2=1pin(PD4) /
// SW_3=20pin(PD3) / SW_4=2pin(PD5) と、STATEレジスタのビット位置の対応が崩れていないか、
// およびアクティブLow・内部プルアップ入力としての設定を回帰テストする。

#include <assert.h>
#include <stdio.h>

#include "ch32fun.h" // test/stub/ch32fun.h (ホストスタブ)

#include "module_config.h"
#include "switches.h"
#include "switches_debounce.h"

// SW_PINS の並び (= STATEレジスタのビット順) に対応する期待ピン。
static const uint8_t EXPECTED_PINS[SW_COUNT] = {PD2, PD4, PD3, PD5};

// 生レベルを count 回サンプリングして確定状態を得る。
static uint8_t sample_times(int count) {
    for (int i = 0; i < count; i++) {
        switches_task();
    }
    return switches_get_state();
}

// SW_PINS が実基板の配線どおりで、ビット位置と1対1に対応している。
static void test_pin_assignment(void) {
    for (int i = 0; i < SW_COUNT; i++) {
        assert(SW_PINS[i] == EXPECTED_PINS[i]);
    }
    assert(SW_PINS[SW_BIT_SW1] == PD2);
    assert(SW_PINS[SW_BIT_SW2] == PD4);
    assert(SW_PINS[SW_BIT_SW3] == PD3);
    assert(SW_PINS[SW_BIT_SW4] == PD5);

    // 同じピンを2つのSWへ割り当てていない。
    for (int i = 0; i < SW_COUNT; i++) {
        for (int j = i + 1; j < SW_COUNT; j++) {
            assert(SW_PINS[i] != SW_PINS[j]);
        }
    }
}

// switches_init() は4本すべてを内部プルアップ入力に設定する (出力にしない = マトリクスの
// 行駆動を行わない)。
static void test_init_configures_pullup_inputs(void) {
    stub_gpio_reset();
    switches_init();

    for (int i = 0; i < SW_COUNT; i++) {
        uint8_t pin = SW_PINS[i];
        assert(stub_gpio.mode_set[pin]);
        assert(stub_gpio.mode[pin] == GPIO_CFGLR_IN_PUPD);
        assert(stub_gpio.level[pin] == FUN_HIGH); // プルアップ選択のためHighを書く
    }

    // SW以外のピンには一切触らない。
    assert(!stub_gpio.mode_set[PC1]);
    assert(!stub_gpio.mode_set[PC4]);
    assert(!stub_gpio.mode_set[PA1]);
}

// 押下(Low)はビットが立ち、開放(High)はビットが落ちる(アクティブLow)。
static void test_active_low_per_switch(void) {
    for (int i = 0; i < SW_COUNT; i++) {
        stub_gpio_reset();
        switches_init();

        // 全ピンHigh = 全SW開放。
        assert(sample_times(SWITCHES_DEBOUNCE_STABLE_SAMPLES) == 0);

        stub_gpio.level[SW_PINS[i]] = FUN_LOW;
        uint8_t state = sample_times(SWITCHES_DEBOUNCE_STABLE_SAMPLES);
        assert(state == (uint8_t)(1u << i));
        assert((state & 0xF0u) == 0);

        stub_gpio.level[SW_PINS[i]] = FUN_HIGH;
        assert(sample_times(SWITCHES_DEBOUNCE_STABLE_SAMPLES) == 0);
    }
}

// 論理名 (PGM×SRC) と物理ピンの対応。STATE契約 (親仕様書 §4.5) の回帰テスト。
static void test_logical_bit_mapping(void) {
    stub_gpio_reset();
    switches_init();

    stub_gpio.level[PD2] = FUN_LOW; // SW_1 = PGM1×SRC1
    stub_gpio.level[PD3] = FUN_LOW; // SW_3 = PGM2×SRC1
    uint8_t state = sample_times(SWITCHES_DEBOUNCE_STABLE_SAMPLES);
    assert(state == (uint8_t)((1u << SW_BIT_PGM1_SRC1) | (1u << SW_BIT_PGM2_SRC1)));

    // PD4(SW_2)/PD5(SW_4) は押していないのでビットは立たない。
    assert((state & (uint8_t)(1u << SW_BIT_PGM1_SRC2)) == 0);
    assert((state & (uint8_t)(1u << SW_BIT_PGM2_SRC2)) == 0);
}

// 走査ごとにピンへ書き込まない (直読みのみ)。マトリクス走査へ戻ると、非選択行の駆動で
// ここが増えるため回帰検出になる。
static void test_task_does_not_drive_pins(void) {
    stub_gpio_reset();
    switches_init();

    uint8_t writes_after_init[SW_COUNT];
    for (int i = 0; i < SW_COUNT; i++) {
        writes_after_init[i] = stub_gpio.write_count[SW_PINS[i]];
    }

    sample_times(10);

    for (int i = 0; i < SW_COUNT; i++) {
        assert(stub_gpio.write_count[SW_PINS[i]] == writes_after_init[i]);
    }
    assert(stub_gpio.delay_us_total == 0); // 行切替の整定待ちも不要
}

int main(void) {
    test_pin_assignment();
    test_init_configures_pullup_inputs();
    test_active_low_per_switch();
    test_logical_bit_mapping();
    test_task_does_not_drive_pins();

    printf("test_switches_io: OK\n");
    return 0;
}
